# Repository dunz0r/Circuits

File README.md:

My collection libs, schematics, pcbs
Some done by me, some done by others

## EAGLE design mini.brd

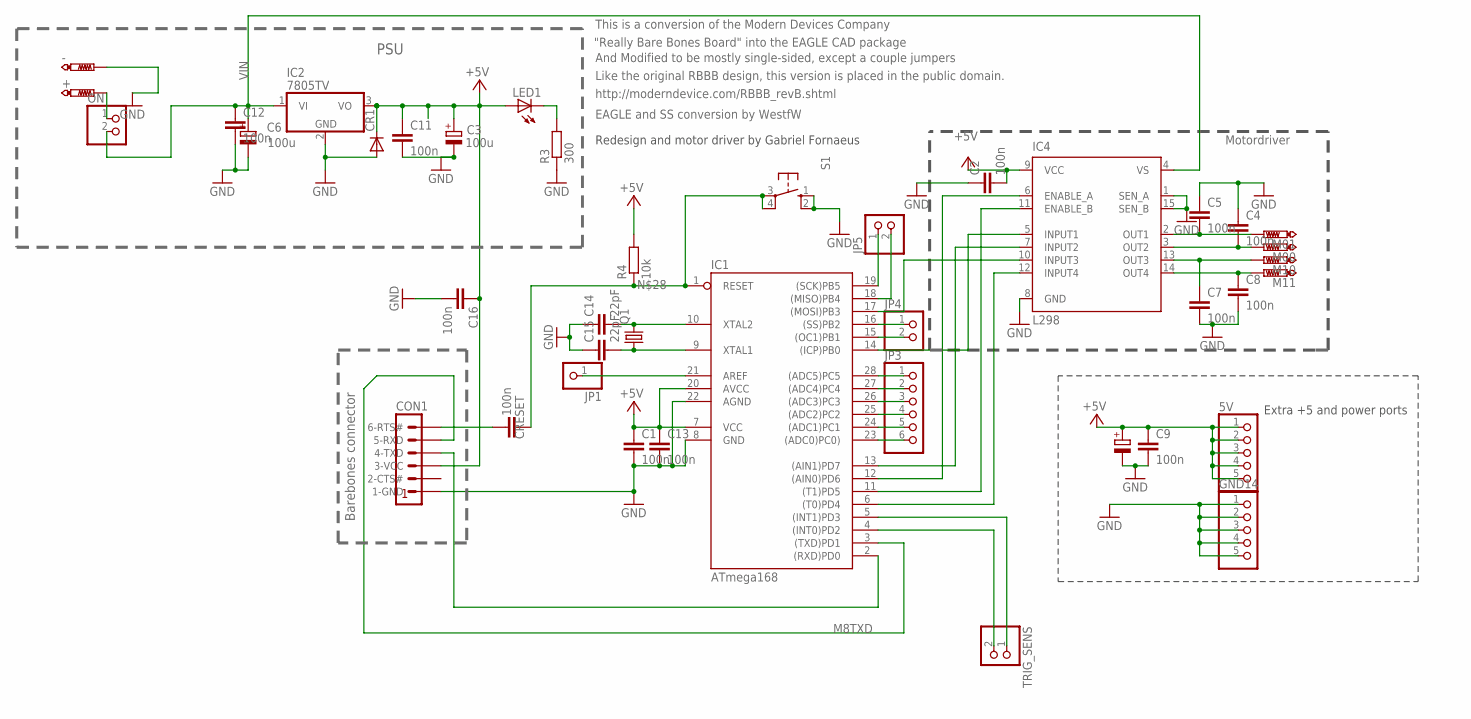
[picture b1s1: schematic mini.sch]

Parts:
5V: PINHD-1X5; 1X05
+: PTR1PAD1-13Y; P1-13Y
-: PTR1PAD1-13Y; P1-13Y
C1, C2, C4, C5, C7, C8, C9, C11, C12, C13, C16: 100n; C025-025X050
C3, C6, C10: 100u; E2,5-7
C14, C15: 22pF; C025-024X044
CON1: FTDI-TTL232R; MA06-1
CR1: DIODE-1ARECT-2V; DO41-2V
CRESET: 100n; C025-025X050
GND14: PINHD-1X5; 1X05
IC1: ATmega168; DIL28-3
IC2: 7805TV; TO220V
IC4: L298; MULTIWATT-15
JP1: PINHD-1X1; 1X01
JP3: PINHD-1X6; 1X06
JP4, JP5: PINHD-1X2; 1X02
LED1: LED3MM
M00, M01, M10, M11: PTR1PAD1-13Y; P1-13Y
ON: PINHD-1X2; 1X02
Q1: CRYSTALHC49S; HC49/S
R3: 300; 0204/7
R4: 10k; 0204/7
S1: 10-XX; B3F-10XX
TRIG_SENS: PINHD-1X2; 1X02

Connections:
+5V: 5V.1, 5V.2, 5V.3, 5V.4, 5V.5, C1.1, C2.2, C3.+, C9.1, C10.+, C11.1, C13.1, C16.1, CON1.3 (3-VCC), CR1.C, IC1.7 (VCC), IC1.20 (AVCC), IC2.3 (VO), IC4.9 (VCC), LED1.A, R4.2
GND: -.TP, C1.2, C2.1, C3.-, C4.1, C5.1, C6.-, C7.2, C8.2, C9.2, C10.-, C11.2, C12.2, C13.2, C14.1, C15.1, C16.2, CON1.1 (1-GND), CR1.A, GND14.1, GND14.2, GND14.3, GND14.4, GND14.5, IC1.8 (GND), IC1.22 (AGND), IC2.2 (GND), IC4.1 (SEN_A), IC4.8 (GND), IC4.15 (SEN_B), R3.1, S1.1 (S), S1.2 (S1)
M8RXD: CON1.4 (4-TXD), IC1.2 ((RXD)PD0)
M8TXD: CON1.5 (5-RXD), IC1.3 ((TXD)PD1)
unnamed: IC1.28 ((ADC5)PC5), JP3.1
unnamed: LED1.K (C), R3.2
unnamed: IC1.13 ((AIN1)PD7), IC4.7 (INPUT2)
unnamed: IC1.27 ((ADC4)PC4), JP3.2
unnamed: IC1.26 ((ADC3)PC3), JP3.3
unnamed: C15.2, IC1.9 (XTAL1), Q1.1
unnamed: C14.2, IC1.10 (XTAL2), Q1.2
unnamed: CON1.6 (6-RTS#), CRESET.1
unnamed: IC1.11 ((T1)PD5), IC4.11 (ENABLE_B)
unnamed: IC1.6 ((T0)PD4), IC4.12 (INPUT4)
unnamed: C7.1, IC4.13 (OUT3), M10.TP
unnamed: IC1.25 ((ADC2)PC2), JP3.4
unnamed: C8.1, IC4.14 (OUT4), M11.TP
unnamed: IC1.14 ((ICP)PB0), IC4.5 (INPUT1)
unnamed: C4.2, IC4.3 (OUT2), M00.TP
unnamed: IC1.24 ((ADC1)PC1), JP3.5
unnamed: IC1.23 ((ADC0)PC0)), JP3.6
unnamed: C5.2, IC4.2 (OUT1), M01.TP
unnamed: IC1.17 ((MOSI)PB3), IC4.10 (INPUT3)
unnamed: IC1.12 ((AIN0)PD6), IC4.6 (ENABLE_A)
unnamed: +.TP, ON.1
unnamed: IC1.16 ((SS)PB2), JP4.1
unnamed: IC1.15 ((OC1)PB1), JP4.2
unnamed: IC1.18 ((MISO)PB4), JP5.2
unnamed: IC1.19 ((SCK)PB5), JP5.1
unnamed: CRESET.2, IC1.1 (RESET), R4.1, S1.3, S1.4 (P1)
unnamed: IC1.21 (AREF), JP1.1
unnamed: IC1.5 ((INT1)PD3), TRIG_SENS.1
unnamed: IC1.4 ((INT0)PD2), TRIG_SENS.2
VIN: C6.+, C12.1, IC2.1 (VI), IC4.4 (VS), ON.2

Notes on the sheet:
Barebones connector
http://moderndevice.com/RBBB_revB.shtml
This is a conversion of the Modern Devices Company
"Really Bare Bones Board" into the EAGLE CAD package
And Modified to be mostly single-sided, except a couple jumpers
Like the original RBBB design, this version is placed in the public domain.
EAGLE and SS conversion by WestfW
Motordriver
Extra +5 and power ports
Redesign and motor driver by Gabriel Fornaeus
PSU

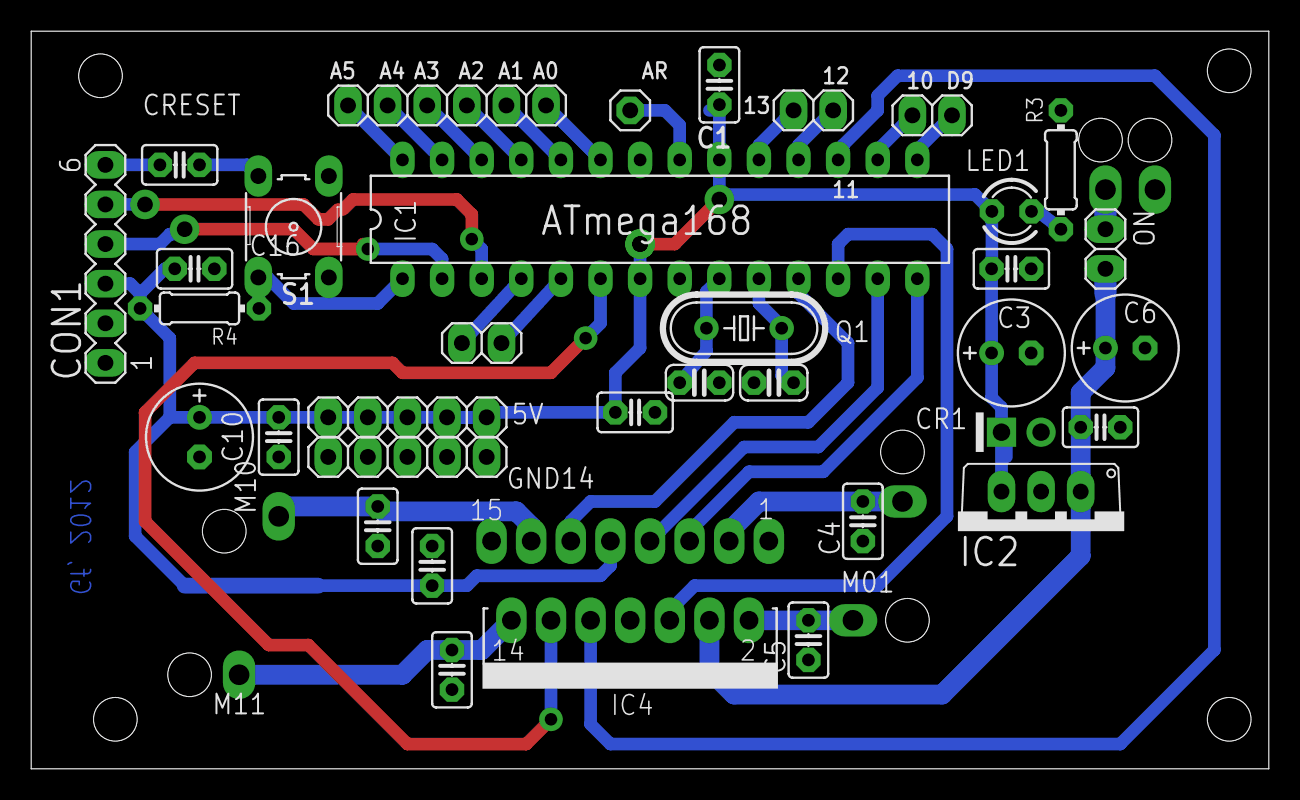
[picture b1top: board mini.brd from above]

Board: 2 copper layers, 79.4 x 47.3 mm, 41 parts (0 on the bottom side), 34 nets.

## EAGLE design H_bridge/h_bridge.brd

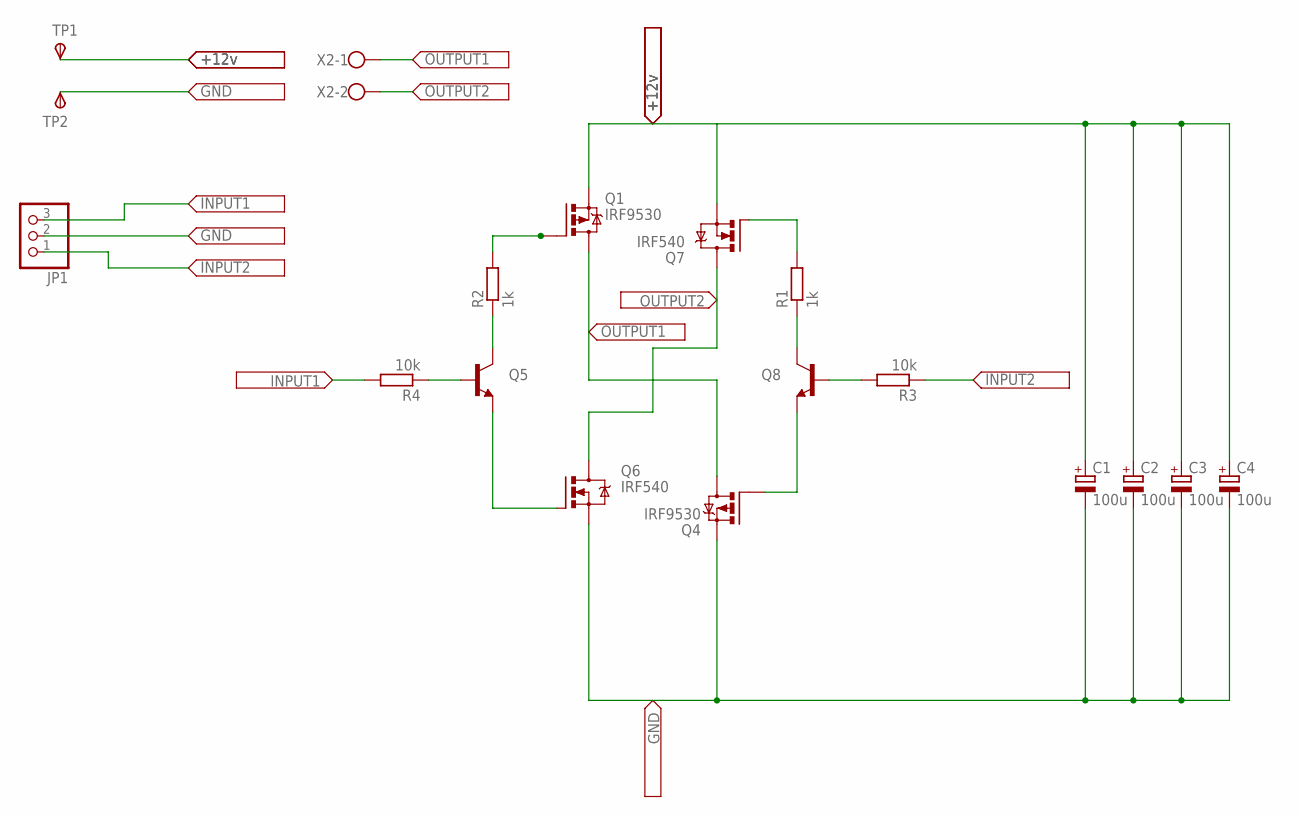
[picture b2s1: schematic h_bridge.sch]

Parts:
C1, C2, C3, C4: 100u; E2,5-6E
JP1: PINHD-1X3; 1X03
Q1, Q4: IRF9530; TO220BV
Q5, Q8: TRANSISTOR_NPNTO92; TO-92
Q6, Q7: IRF540; TO220BV
R1, R2: 1k; 0207/7
R3, R4: 10k; 0207/7
TP1, TP2: TPSPAD1-17Y; P1-17Y
X2: W237-02P; W237-132

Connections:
+12V: C1.+, C2.+, C3.+, C4.+, Q1.S, Q7.S, TP1.TP
GND: C1.-, C2.-, C3.-, C4.-, JP1.2, Q4.S, Q6.S, TP2.TP
INPUT1: JP1.3, R4.2
INPUT2: JP1.1, R3.1
unnamed: Q5.3 (C), R2.1
unnamed: Q1.G, R2.2
unnamed: Q8.3 (C), R1.1
unnamed: Q4.G, Q8.1 (E)
unnamed: Q5.2 (B), R4.1
unnamed: Q8.2 (B), R3.2
OUTPUT1: Q1.D, Q4.D, X2.1
OUTPUT2: Q6.D, Q7.D, X2.2

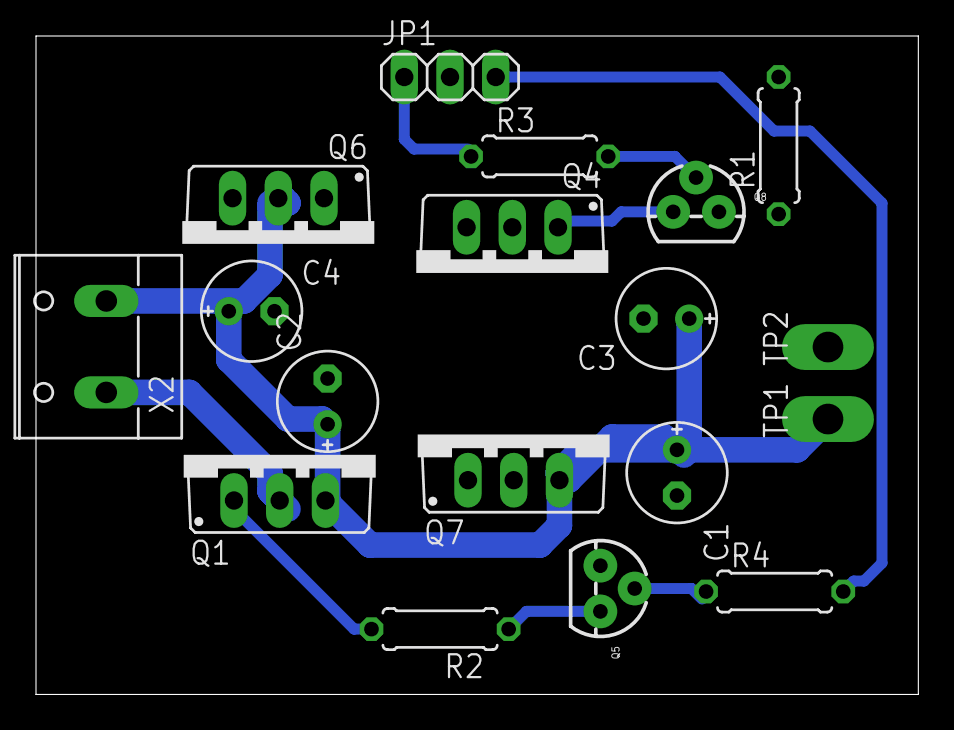
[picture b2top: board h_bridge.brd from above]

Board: 2 copper layers, 49.0 x 36.6 mm, 18 parts (0 on the bottom side), 12 nets.

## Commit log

2013-06-07 Some stuff added
2013-06-07 More files added, some eaglefiles too :O
2013-06-07 Edited README
2014-02-11 Added Amplifier and visualizer
2014-03-23 The timerbox added
2014-08-11 Added some libs and some new circuits
